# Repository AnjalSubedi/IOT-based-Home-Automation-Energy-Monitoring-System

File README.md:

# IOT-based-Home-Automation-Energy-Monitoring-System

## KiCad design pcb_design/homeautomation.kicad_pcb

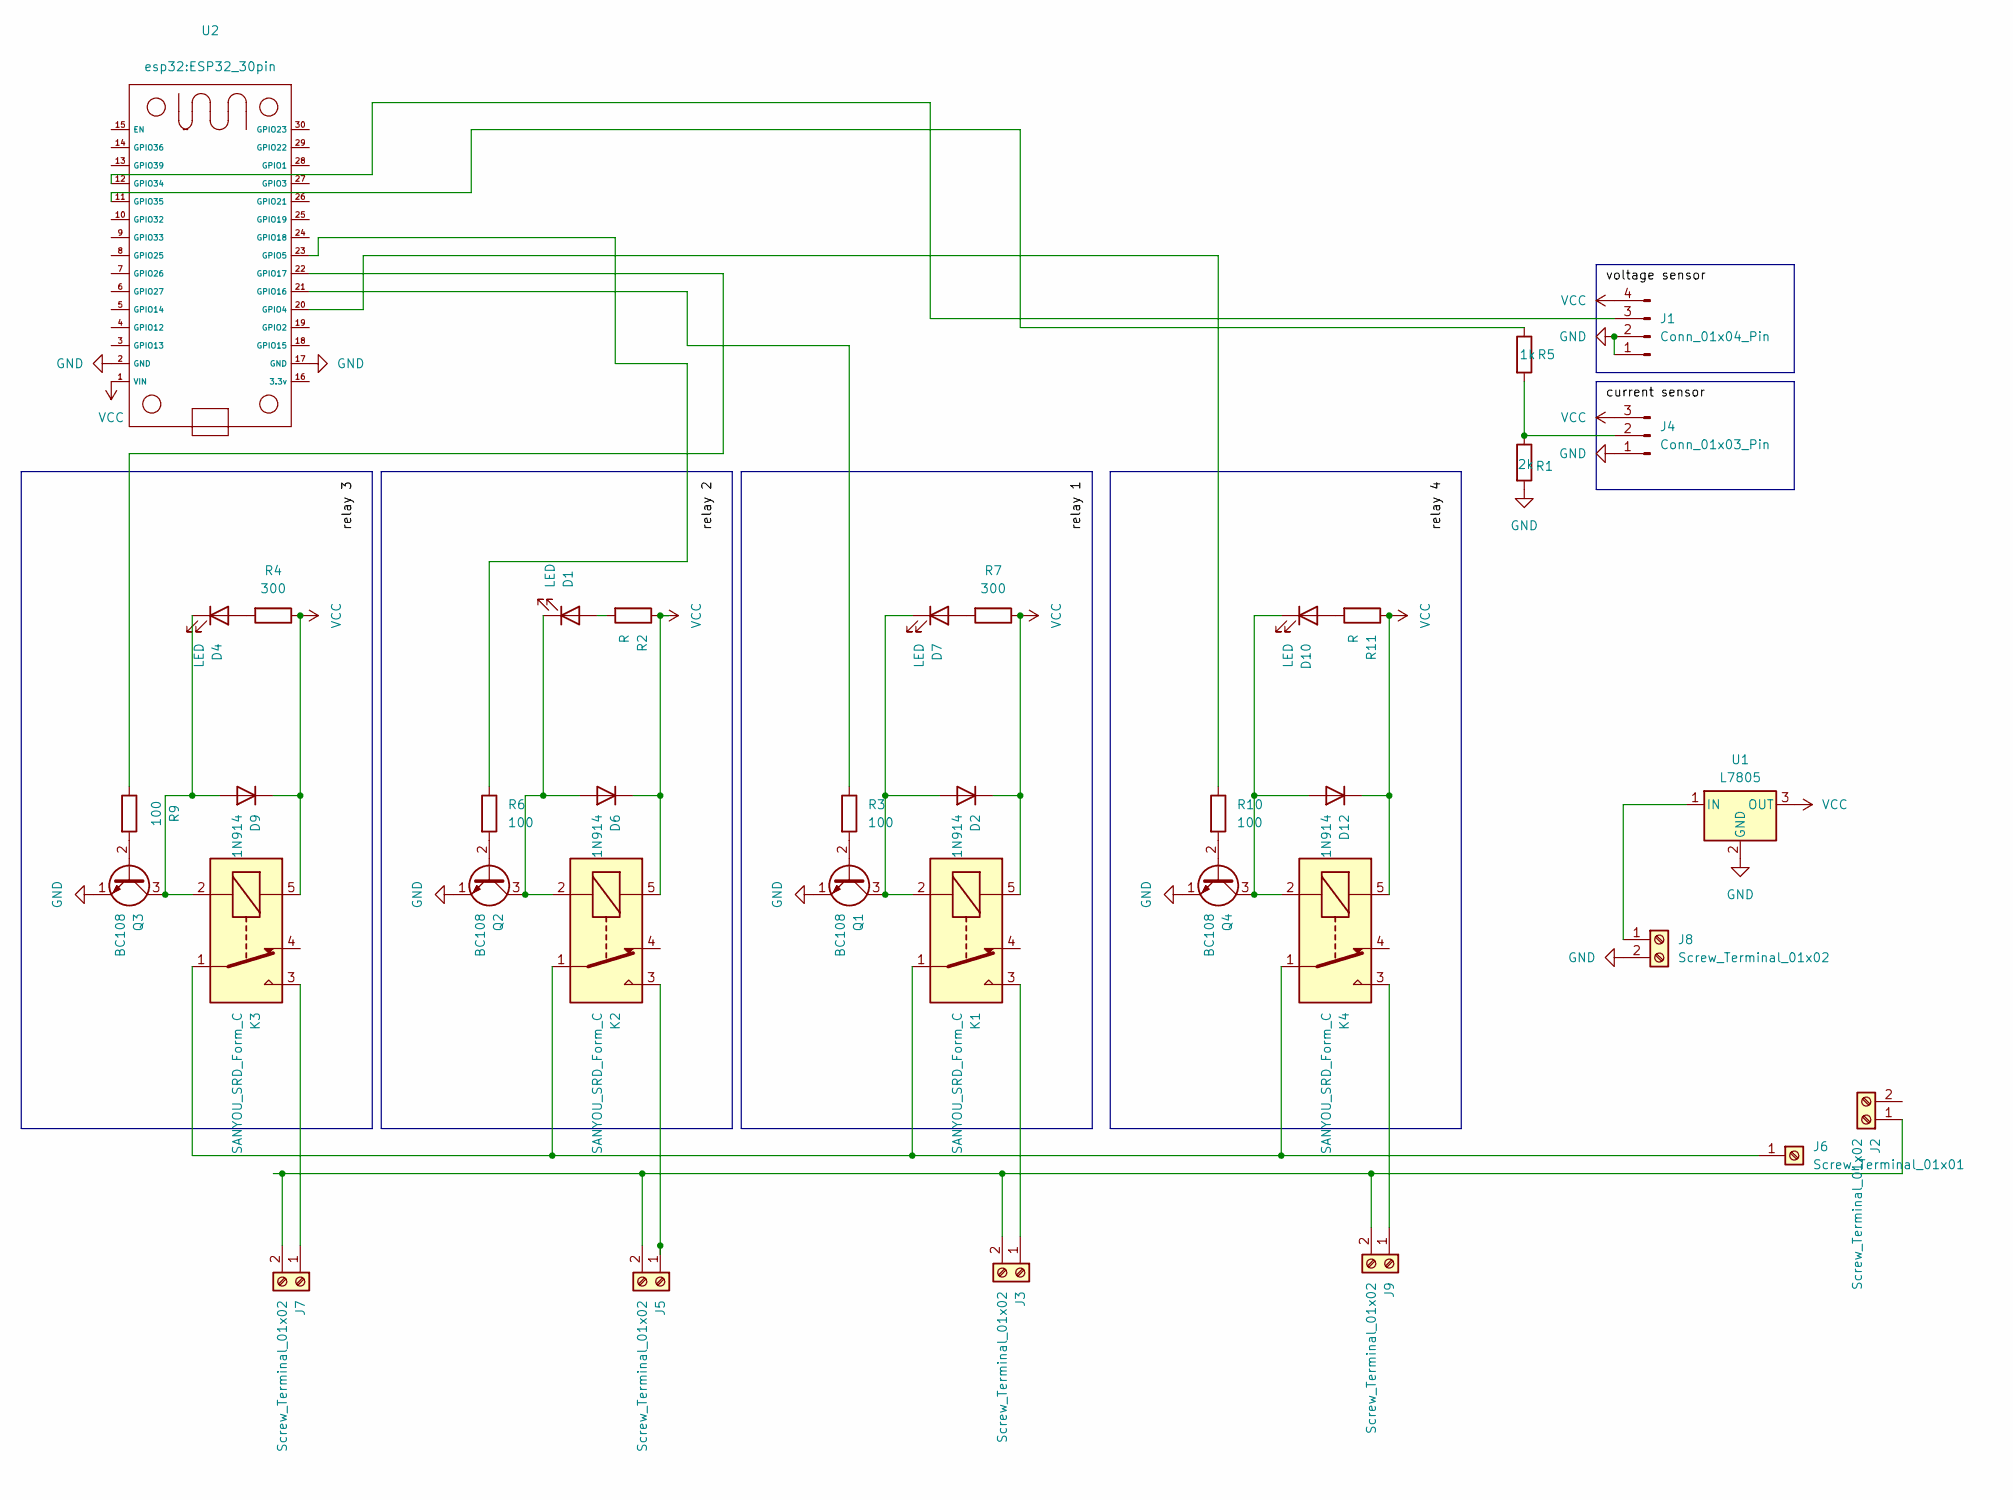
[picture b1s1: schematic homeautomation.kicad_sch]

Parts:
D1, D4, D7, D10: LED; LED_D5.0mm
D2, D6, D9, D12: 1N914; D_DO-35_SOD27_P7.62mm_Horizontal
J1: Conn_01x04_Pin; PinHeader_1x04_P2.54mm_Vertical
J2, J3, J5, J7, J9: Screw_Terminal_01x02; TerminalBlock_bornier-2_P5.08mm
J4: Conn_01x03_Pin; PinHeader_1x03_P2.54mm_Vertical
J6: Screw_Terminal_01x01; TerminalBlock_bornier-2_P5.08mm
J8: Screw_Terminal_01x02; TerminalBlock_MaiXu_MX126-5.0-02P_1x02_P5.00mm
K1, K2, K3, K4: SANYOU_SRD_Form_C; Relay_SPDT_SANYOU_SRD_Series_Form_C
Q1, Q2, Q3, Q4: BC108; TO-92L_Inline_Wide
R1: 2k; R_Axial_DIN0207_L6.3mm_D2.5mm_P10.16mm_Horizontal
R2, R11: R; R_Axial_DIN0207_L6.3mm_D2.5mm_P10.16mm_Horizontal
R3, R6, R9, R10: 100; R_Axial_DIN0207_L6.3mm_D2.5mm_P10.16mm_Horizontal
R4, R7: 300; R_Axial_DIN0207_L6.3mm_D2.5mm_P10.16mm_Horizontal
R5: 1k; R_Axial_DIN0207_L6.3mm_D2.5mm_P10.16mm_Horizontal
U1: L7805; TO-220-3_Vertical
U2: ESP32_30pin

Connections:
GND: J1.1, J1.2, J4.1, J8.2, Q1.1 (E), Q2.1 (E), Q3.1 (E), Q4.1 (E), R1.2, U1.2 (GND), U2.2 (GND), U2.17 (GND)
unnamed: D1.2 (A), R2.2
unnamed: D1.1 (K), D6.2 (A), K2.2, Q2.3 (C)
unnamed: D2.2 (A), D7.1 (K), K1.2, Q1.3 (C)
unnamed: D4.2 (A), R4.2
unnamed: D4.1 (K), D9.2 (A), K3.2, Q3.3 (C)
unnamed: D7.2 (A), R7.2
unnamed: D10.2 (A), R11.2
unnamed: D10.1 (K), D12.2 (A), K4.2, Q4.3 (C)
unnamed: J1.3, U2.12 (GPIO34)
unnamed: J2.1, J3.2, J5.2, J7.2, J9.2
unnamed: J3.1, K1.3
unnamed: J4.2, R1.1, R5.2
unnamed: J5.1, K2.3
unnamed: J6.1, K1.1, K2.1, K3.1, K4.1
unnamed: J7.1, K3.3
unnamed: J8.1, U1.1 (IN)
unnamed: J9.1, K4.3
unnamed: Q1.2 (B), R3.2
unnamed: Q2.2 (B), R6.2
unnamed: Q3.2 (B), R9.2
unnamed: Q4.2 (B), R10.2
unnamed: R10.1, U2.20 (GPIO4)
unnamed: R6.1, U2.23 (GPIO5)
unnamed: R3.1, U2.21 (GPIO16)
unnamed: R9.1, U2.22 (GPIO17)
unnamed: R5.1, U2.11 (GPIO35)
VCC: D2.1 (K), D6.1 (K), D9.1 (K), D12.1 (K), J1.4, J4.3, K1.5, K2.5, K3.5, K4.5, R2.1, R4.1, R7.1, R11.1, U1.3 (OUT), U2.1 (VIN)

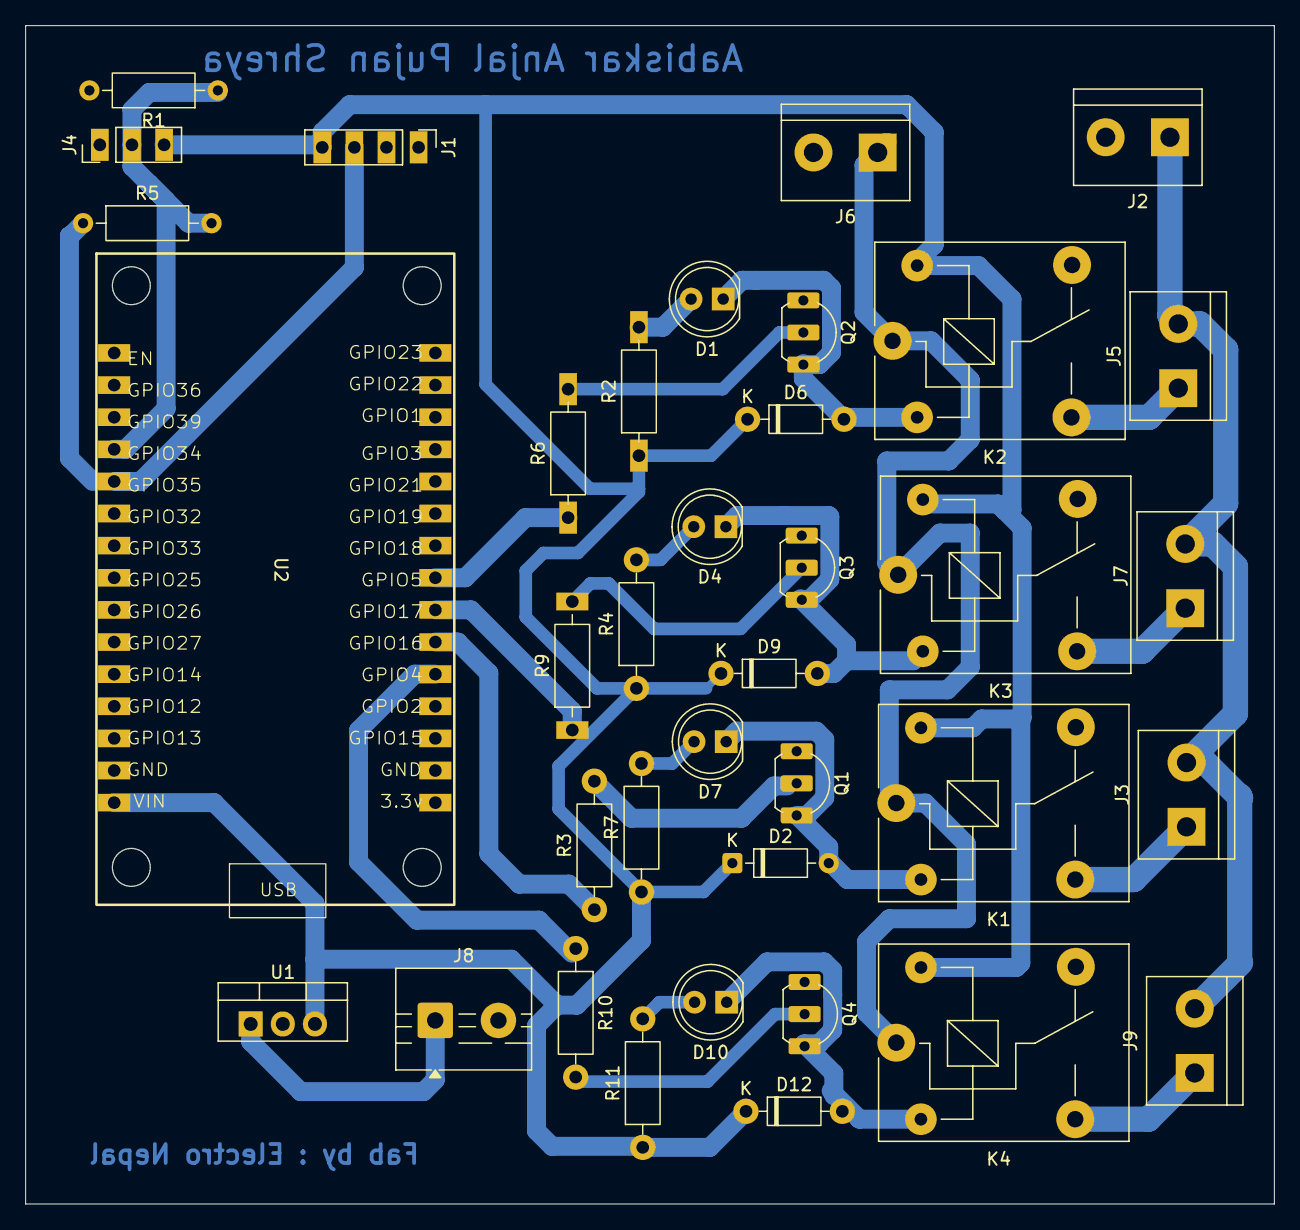
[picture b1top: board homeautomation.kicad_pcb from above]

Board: 2 copper layers, 98.7 x 93.1 mm, 37 parts (0 on the bottom side), 28 nets.

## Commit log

2026-02-13 Initial commit: ESP32 + Node backend
2026-05-04 feat: add real sensor readings (ZMPT101B + SCT-013), relay control, noise floor guard, and energy accumulation
2026-05-11 feat: complete IoT Home Automation & Energy Monitoring System
    - Flutter mobile app (dashboard, relay control, cost estimation, alerts)
    - Node.js REST API + Socket.IO real-time server
    - MQTT integration with HiveMQ Cloud (ESP32 ↔ Server)
    - ESP32 firmware with ZMPT101B voltage + ACS712 current sensing
    - 4-channel relay control via NPN transistor driver
    - NEA tariff-based cost calculation for Nepal
2026-05-11 chore: remove duplicate firmware/ folder (esp32/ is the real firmware)
2026-05-11 refactor: rename esp32/ → firmware/ and flatten folder structure
2026-05-13 kicad pcb file uploaded
2026-05-13 schematic uploaded
